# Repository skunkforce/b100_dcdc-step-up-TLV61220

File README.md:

# edgy_board number b100
This design is part of the [edgy board project](https://github.com/skunkforce/edgy_boards).

# getting started
This repository uses submodules. After cloning use the command 

```$ git submodule update --init --recursive```

to pull the submodules before opening the project with kicad. 

# Tests
Tests can be found in [TESTS.md](TESTS.md)

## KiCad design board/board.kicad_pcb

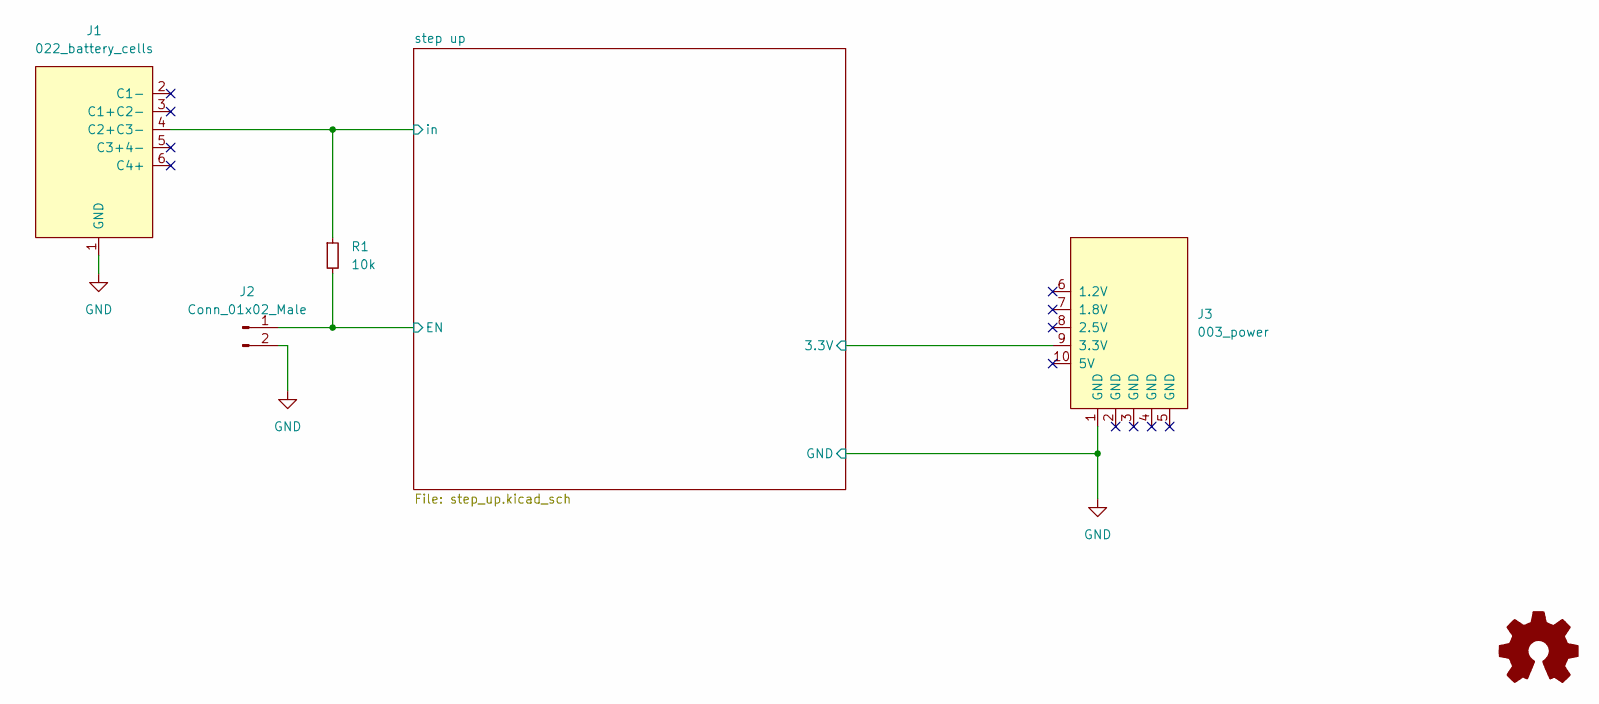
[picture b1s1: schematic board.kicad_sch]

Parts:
J1: 022_battery_cells; on_edge_2x05_device
J2: Conn_01x02_Male; PinHeader_1x02_P2.54mm_Vertical
J3: 003_power; on_edge_2x05_host
LOGO1: Logo_Open_Hardware_Small; OSHW-Symbol_6.7x6mm_SilkScreen
R1: 10k; R_0603_1608Metric

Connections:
/step up/3.3V: J3.9 (3.3V); also elsewhere on the board
/step up/EN: J2.1, R1.2; also elsewhere on the board
/step up/in: J1.4 (C2+C3-), R1.1; also elsewhere on the board
GND: J1.1 (GND), J2.2, J3.1 (GND); also elsewhere on the board

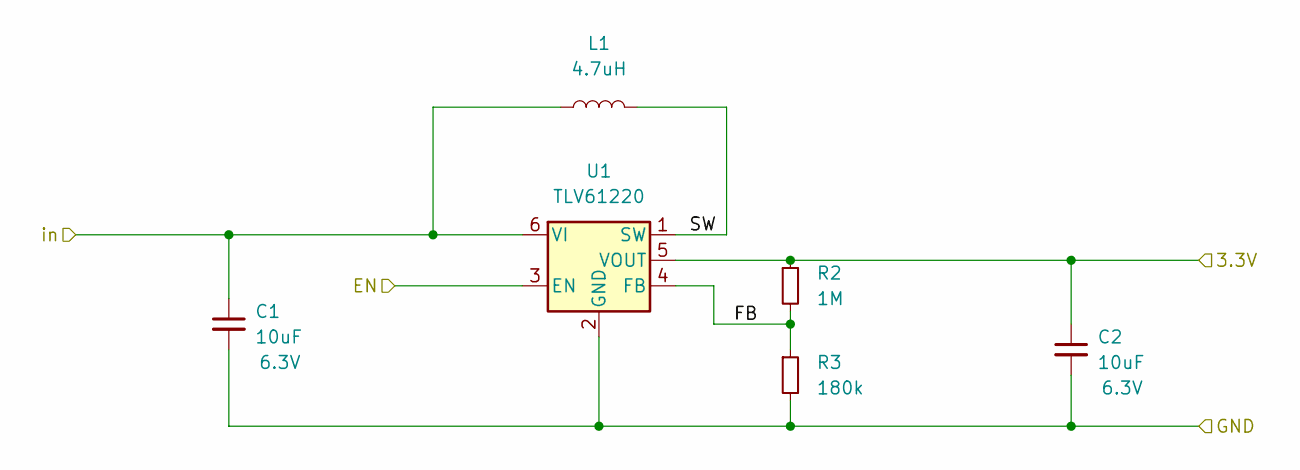
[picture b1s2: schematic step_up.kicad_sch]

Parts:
C1, C2: 10uF; C_0603_1608Metric; Voltage 6.3V
L1: 4.7uH; L_0805_2012Metric; MPN MLZ2012N4R7LTD25; DigiKey_PN 445-16383-1-ND
R2: 1M; R_0603_1608Metric
R3: 180k; R_0603_1608Metric
U1: TLV61220; SOT-23-6

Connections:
/step up/3.3V: C2.1, R2.1, U1.5 (VOUT); also elsewhere on the board
/step up/EN: U1.3 (EN); also elsewhere on the board
/step up/FB: R2.2, R3.1, U1.4 (FB)
/step up/SW: L1.2, U1.1 (SW)
/step up/in: C1.1, L1.1, U1.6 (VI); also elsewhere on the board
GND: C1.2, C2.2, R3.2, U1.2 (GND); also elsewhere on the board

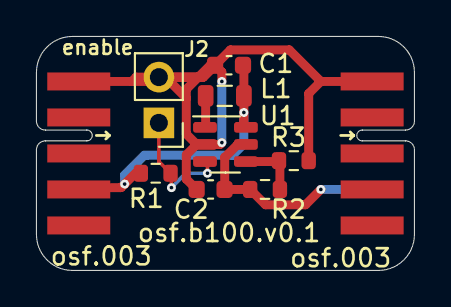
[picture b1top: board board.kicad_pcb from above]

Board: 2 copper layers, 21.0 x 13.0 mm, 11 parts (1 on the bottom side), 6 nets.

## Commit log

2023-02-26 improved documentation
2023-02-26 initial
2023-03-02 moved components for better EMC
2023-03-04 changed input to battery cell connector
2023-03-16 updated tests
